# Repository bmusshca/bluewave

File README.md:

# bluewave
it's a project of ENSICAEN. 
Chief executive Hugo Descoubes 
for student of first year.
# Those two files, are the schematic and the layout made by me. 
it's done with kicad as a software.

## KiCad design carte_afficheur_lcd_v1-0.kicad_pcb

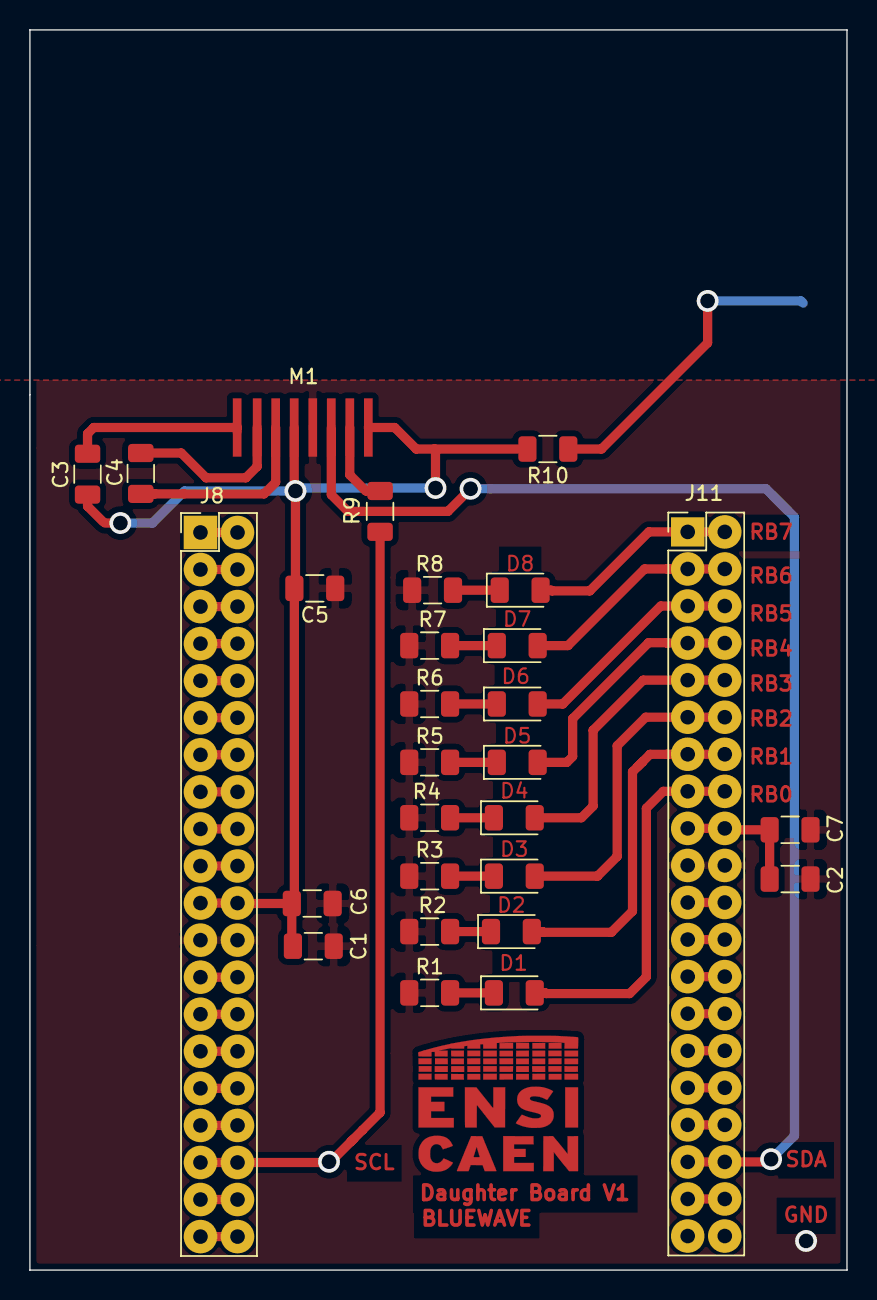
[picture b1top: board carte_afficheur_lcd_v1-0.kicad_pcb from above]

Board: 2 copper layers, 56.0 x 85.0 mm, 29 parts (0 on the bottom side), 51 nets.

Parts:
C1, C2, C3, C4: 1µf; C_1206_3216Metric
C5: 100nf; C_1206_3216Metric
C6, C7: 0.1µf; C_1206_3216Metric
D1, D2, D3, D4, D5, D6, D7, D8: LED_ALT; LED_1206_3216Metric
J1: Conn_01x02; PinSocket_1x02_P2.54mm_Vertical
J8: J8; PinHeader_2x20_P2.54mm_Vertical
J11: J11; PinHeader_2x20_P2.54mm_Vertical
M1: LCD-ALPHA1602; LCD-1602-NEW
R1, R2, R3, R4, R7, R8: 1k; R_1206_3216Metric
R5, R6: 10k; R_1206_3216Metric
R9: 0; R_1206_3216Metric
R10: 100; R_1206_3216Metric

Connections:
/TVDD: C1.2, C2.1, C3.2, C5.2, C6.2, C7.2, J8.21, J8.22, J11.17, J11.18, M1.4, M1.8, R10.2
GND: C1.1, C2.2, C5.1, C6.1, C7.1, J1.1, J8.23, J8.24, J11.19, J11.20, M1.5, R1.1, R2.1, R3.1, R4.1, R5.1, R6.1, R7.1, R8.1
unnamed: C3.1, M1.1
unnamed: C4.1, M1.2
unnamed: C4.2, M1.3
unnamed: D1.1, R1.2
unnamed: D2.1, R2.2
unnamed: D3.1, R3.2
unnamed: D4.1, R4.2
unnamed: D5.1, R5.2
unnamed: D6.1, R6.2
unnamed: D7.1, R7.2
unnamed: D8.1, R8.2
unnamed: J1.2, R10.1
unnamed: M1.7, R9.1
RA0: J8.3, J8.4
RA1: J8.5, J8.6
RA2: J8.7, J8.8
RA3: J8.9, J8.10
RA4: J8.11, J8.12
RA5: J8.13, J8.14
RA6: J8.27, J8.28
RA7: J8.25, J8.26
RB0: D1.2, J11.15, J11.16
RB1: D2.2, J11.13, J11.14
RB2: D3.2, J11.11, J11.12
RB3: D4.2, J11.9, J11.10
RB4: D5.2, J11.7, J11.8
RB5: D6.2, J11.5, J11.6
RB6: D7.2, J11.3, J11.4
RB7: D8.2, J11.1, J11.2
RC0: J8.29, J8.30
RC1: J8.31, J8.32
RC2: J8.33, J8.34
RC3: J8.35, J8.36, R9.2
RC4: J11.35, J11.36, M1.6
RC5: J11.33, J11.34
RC6: J11.31, J11.32
RC7: J11.29, J11.30
RD0: J8.37, J8.38
RD1: J8.39, J8.40
RD2: J11.39, J11.40
RD3: J11.37, J11.38
RD4: J11.27, J11.28
RD5: J11.25, J11.26
RD6: J11.23, J11.24
RD7: J11.21, J11.22
RE0: J8.15, J8.16
RE1: J8.17, J8.18
RE2: J8.19, J8.20
RE3: J8.1, J8.2
